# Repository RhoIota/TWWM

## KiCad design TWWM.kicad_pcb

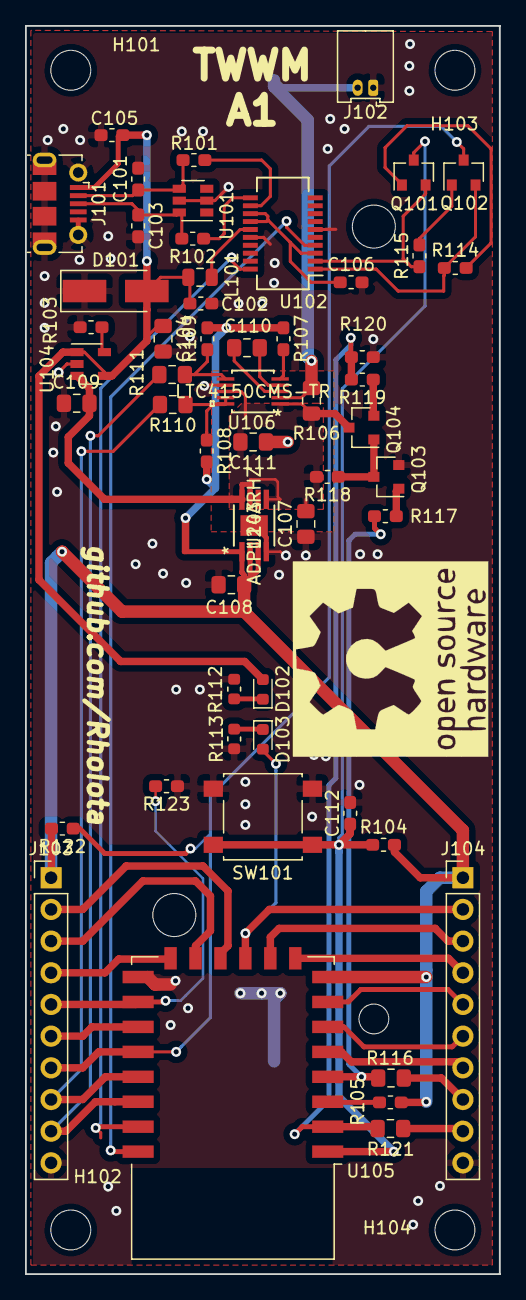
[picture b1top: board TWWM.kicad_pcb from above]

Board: 2 copper layers, 38.0 x 100.1 mm, 59 parts (1 on the bottom side), 48 nets.

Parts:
C101, C103: 47p; C_0603_1608Metric_Pad1.05x0.95mm_HandSolder
C102, C106, C112: 100n; C_0603_1608Metric_Pad1.05x0.95mm_HandSolder
C104, C107, C108, C109, C110, C111: 4u7; C_0805_2012Metric_Pad1.15x1.40mm_HandSolder
C105: 10n; C_0603_1608Metric_Pad1.05x0.95mm_HandSolder
D101: SMAJ5.0CA; D_SMA_Handsoldering
D102, D103: rt; LED_0603_1608Metric
H101, H102, H103, H104: MH; MountingHole_3.2mm_M3
J101: USB_B_Micro; USB_Micro-B_Molex-105017-0001
J102: Molex 51021-0200; Molex_PicoBlade_53048-0210_1x02_P1.25mm_Horizontal
J103, J104: Conn_01x10_Male; PinHeader_1x10_P2.54mm_Vertical
J105: 18650; BatteryHolder_Keystone_1042_1x18650
L101: 600R/2A; L_0805_2012Metric
Q101, Q102, Q103: Q_NPN_BEC; SOT-23
Q104: Q_PMOS_GSD; SOT-23
R101, R102: 27R; R_0603_1608Metric_Pad1.05x0.95mm_HandSolder
R103: 2k; R_0603_1608Metric_Pad1.05x0.95mm_HandSolder
R104, R105, R107, R108, R109, R114, R115, R117, R118, R120, R122, R123: 10k; R_0603_1608Metric_Pad1.05x0.95mm_HandSolder
R106: 0R1; R_0805_2012Metric_Pad1.15x1.40mm_HandSolder
R110, R111, R116, R121: 0R; R_0805_2012Metric_Pad1.15x1.40mm_HandSolder
R112, R113: 220R; R_0603_1608Metric
R119: 33k; R_0603_1608Metric_Pad1.05x0.95mm_HandSolder
SW101: SW_Push; SW_SPST_B3S-1000
U101: SN65220; SOT-23-6
U102: FT231XS; SSOP-20_3.9x8.7mm_P0.635mm
U103: ADP124ARHZ
U104: MCP73812T-420I-OT; SOT-23-5
U105: ESP-12E
U106: LTC4150CMS-TR

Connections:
+3V3: C108.2, J103.1, J104.1, R104.2, R105.2, R107.1, R108.2, R109.2, R122.2, U103.1, U103.2, U103.3, U105.8
+5V: C102.1, C104.1, C105.1, D101.2, D102.2, J101.1, L101.2, U104.1, U104.4
+BATT: C107.2, C109.2, C111.2, Q104.3, R106.2, R118.2, U103.5, U103.7, U103.8, U104.3, U106.1, U106.8
/ADC: J104.9, R121.2
/ADC_R: R119.2, R120.1, R121.1, U105.2
/BATT+: J102.2, J105.2, R106.1, U106.2
/CC_INT: R108.1, R110.1, U106.9, U106.10
/CC_POL: R109.1, R111.1, U106.6
/CS: J104.4, U105.9
/D+: C103.1, J101.3, R102.2, U101.6
/D-: C101.1, J101.2, R101.2, U101.4
/FT_3V3: C106.1, U102.3, U102.13, U102.14
/GPIO0: J103.7, Q102.3, R122.1, U105.18
/GPIO2: J103.6, U105.17
/GPIO4: J103.8, R110.2, U105.19
/GPIO5: J103.9, R111.2, U105.20
/GPIO9: D103.2, J104.2, U105.11
/GPIO10: J103.2, U105.12
/GPIO12: J104.6, U105.6
/GPIO13: J104.5, U105.7
/GPIO14: J104.7, U105.5
/GPIO15: J103.5, R123.2, U105.16
/GPIO16: J104.8, R116.2
/GPIO16_R: R116.1, R117.2, U105.4
/MISO: J104.3, U105.10
/MOSI: J103.3, U105.13
/SCLK: J103.4, U105.14
/UART_RX: U102.4, U105.22
/UART_TX: U102.20, U105.21
/~DTR~: Q102.2, R114.1, U102.1
/~RST~: C112.1, Q101.3, R104.1, SW101.1, U105.1
/~RTS~: Q101.2, R115.1, U102.2
GND: C101.2, C102.2, C103.2, C104.2, C105.2, C106.2, C107.1, C108.1, C109.1, C111.1, C112.2, D101.1, J101.5, J101.6, J102.1, J103.10, J104.10, J105.1, Q103.2, R103.1, R112.1, R113.1, R120.2, R123.1, SW101.2, U101.2, U101.5, U102.6, U102.16, U103.4, U103.9, U104.2, U105.15, U106.7
unnamed: C110.1, U106.4
unnamed: C110.2, U106.3
unnamed: D102.1, R112.2
unnamed: D103.1, R113.2
unnamed: L101.1, U102.15
unnamed: Q101.1, R114.2
unnamed: Q102.1, R115.2
unnamed: Q103.1, R117.1
unnamed: Q103.3, Q104.1, R118.1
unnamed: Q104.2, R119.1
unnamed: R101.1, U102.12
unnamed: R102.1, U102.11
unnamed: R103.2, U104.5
unnamed: R105.1, U105.3
unnamed: R107.2, U106.5

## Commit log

2020-03-12 -add: first commit of TWWM project
2020-08-13 -mod: update from A0 to A1: switched Tx and Rx. 10k pullup to GPIO0, 10k pulldown to GPIO15

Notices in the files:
parts and their libraries:
Copyright 2016 Accelerated Designs. All rights reserved.
